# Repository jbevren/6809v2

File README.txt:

6809v2 single-board computer

(c) 2018 David Wood

This system is a 3.68mhz 6809-based microcomputer with 128k RAM and 8K rom.  It is intended to run 6809-based operating systems that run within 64k of RAM such as FLEX or OS-9 Level I.

All I/O services are provided via a 68681 DUART, either via one of its serial ports or via the extra GPIO pins on the device.

This documentation is primarily a placeholder and will likely be improved as time goes on(TM). ;-)

System memory map:

0000-DFFF	System RAM
E000-FEFF	System ROM  (ROMON=high) or System RAM(ROMON=low)
FF00-FF0F	68681 DUART (see below for I/O definitions)
FF10-FFDF	reserved: Don't use
FFE0-FFFF	System ROM  (ROMON=high) or System RAM(ROMON=low)

DUART I/O Map:
IP0		CTS port A
IP1		CTS port B
IP2		DCD port A (not routed)
IP3		DCD port B (not routed)
IP4		n/c
IP5		SD Data input	Input from Micro SD

OP0		RTS port A
OP1		RTS port B
OP2		RAM A16		A16 to RAM
OP3		RAM A17		A17 to RAM (128k has CE2 here)
OP4		ROMON		High enables the 2764 eprom
OP5		SDCK		Clock output to Micro SD
OP6		SDDO		Data output to Micro SD
OP7		SDCS		Chip select output to Micro SD
		NOTE: The 68681 sets all outputs high on reset
		NOTE: The 68681 inverts its output port bits

A summary of programming-related information is also printed on the pcb.

The memory fitted with a standard 128k-256k sram.  A 512k device can be fitted but the board lacks sufficient hardware to bankswitch more than 256k.
A jumper bridge under the SRAM will allow disconnecting A18 from ground.

Directories:
kicad/		Kicad v<5.0 files used to design the board
sbug/		S-BUG port to the 6809v2 SBC (working)
tests/		Prototype test code segments
sdcard/		SD-Card code (not yet finished)

** Many thanks to Dolo@hackaday.IO for the sdcard sample code and permission for the author to use it as long as the code for the firmware remains free and open! **

License: CC:SA license v4.0
I encourage the sharing and adaptation of this design as long as some credit to me is given in the firmware and/or board design.

Reach me at jbevren@gmail.com

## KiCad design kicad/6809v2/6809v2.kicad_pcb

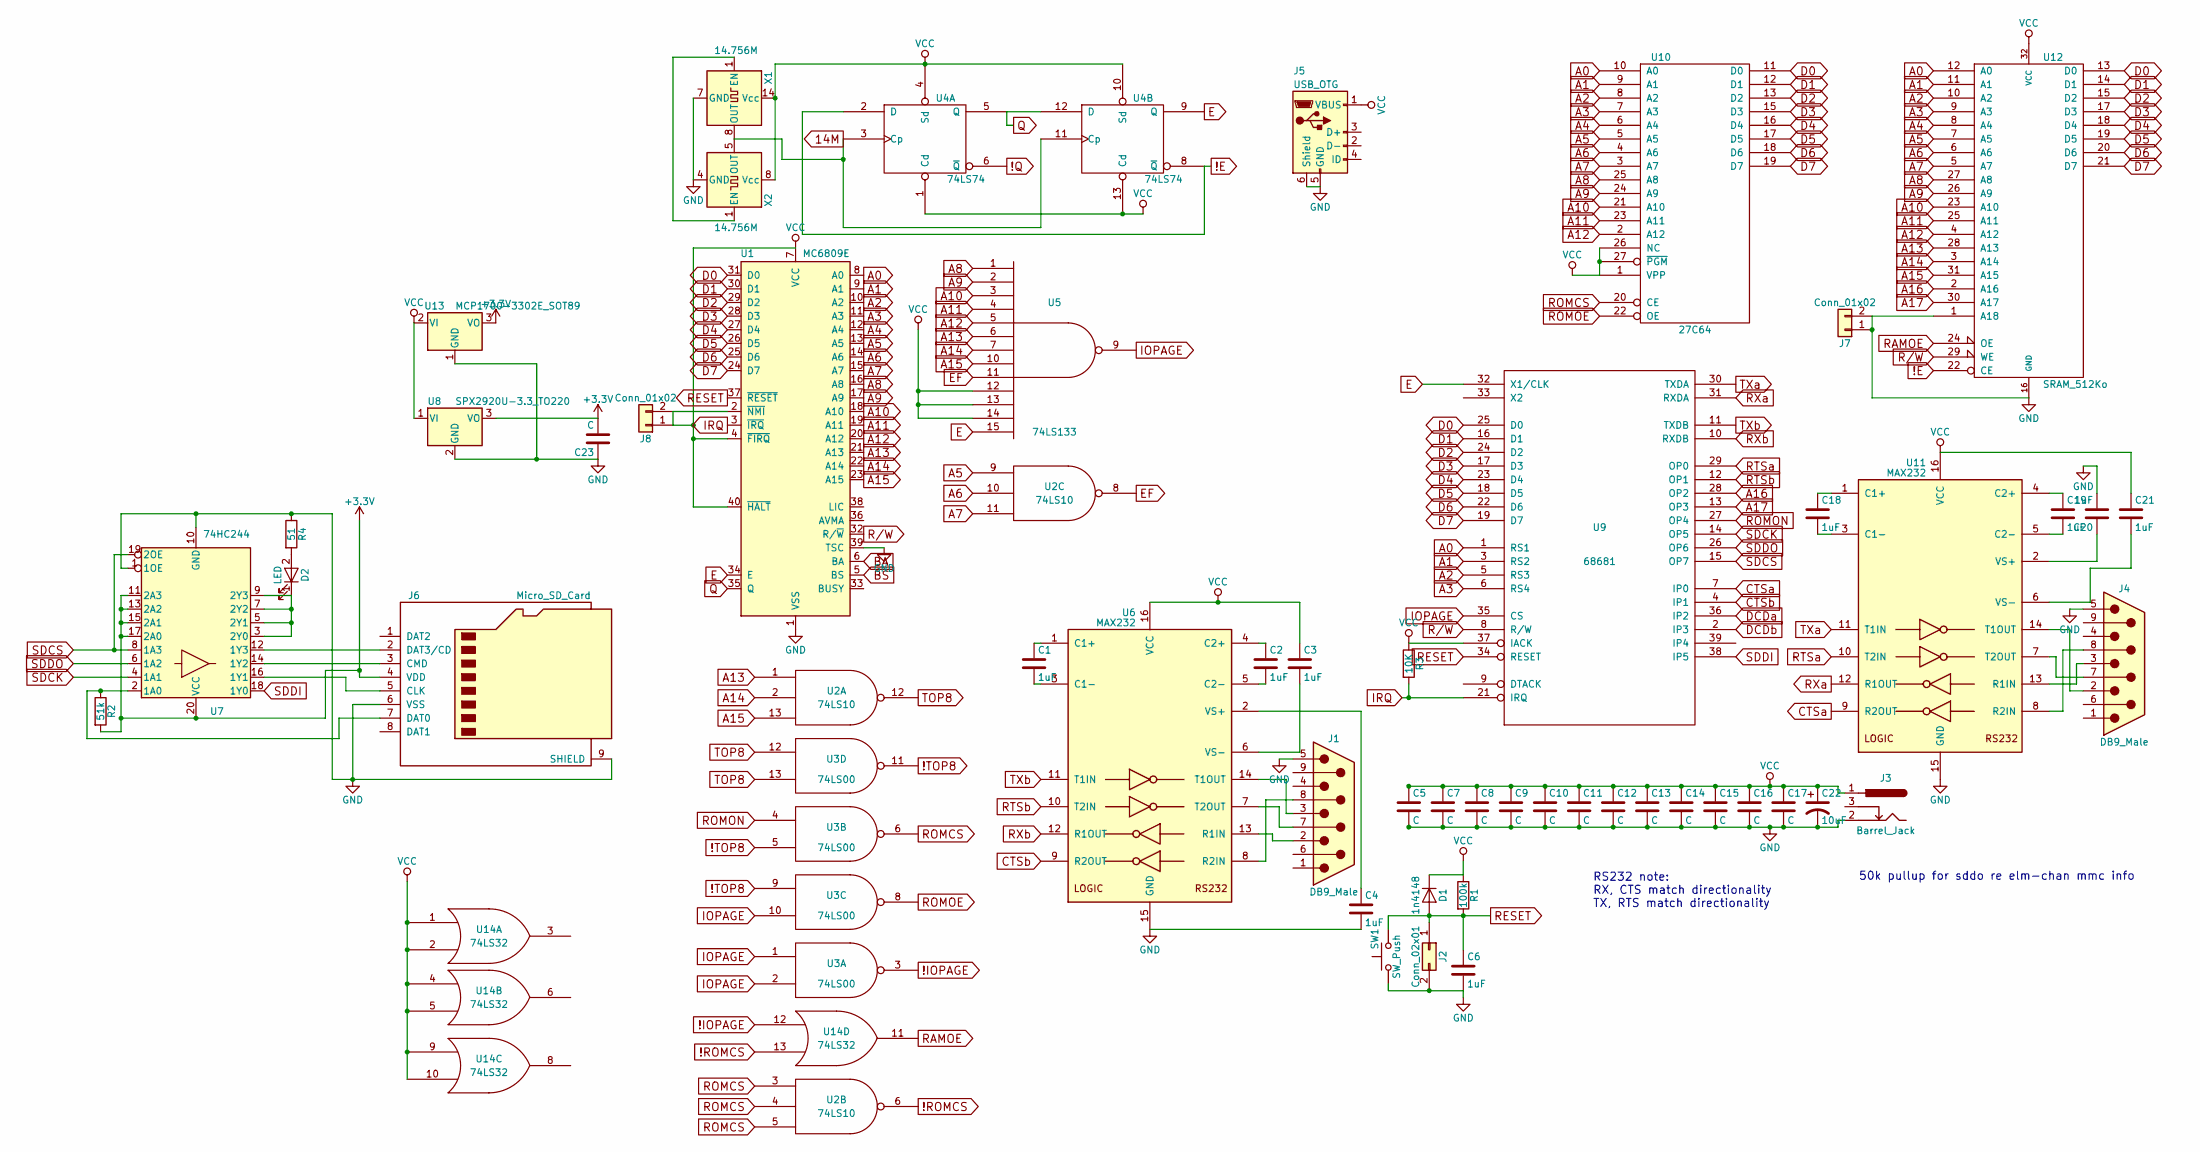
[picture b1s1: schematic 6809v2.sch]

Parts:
C1, C2, C3, C4, C18, C19, C20, C21: 1uF; CP_Radial_D5.0mm_P2.00mm
C5, C7, C8, C9, C10, C11, C12, C13, C14, C15, C16, C17: C; C_Disc_D5.0mm_W2.5mm_P2.50mm
C6: 1uF; C_Disc_D5.0mm_W2.5mm_P2.50mm
C22: 10uF; CP_Radial_D5.0mm_P2.50mm
C23: C; C_Disc_D5.0mm_W2.5mm_P5.00mm
D1: 1n4148; D_A-405_P7.62mm_Horizontal
D2: LED; LED_D5.0mm
J1, J4: DB9_Male; DB9M_CI
J2: Conn_02x01; Pin_Header_Straight_2x01_Pitch2.54mm
J3: Barrel_Jack; BARREL_JACK
J5: USB_OTG; USB_Micro-B_Molex_47346-0001
J6: Micro_SD_Card; MicroSd_Wurth_693072010801
J7, J8: Conn_01x02; Test_Point_2Pads_Pitch2.54mm_Drill0.8mm
R1: 100k; R_Axial_DIN0207_L6.3mm_D2.5mm_P2.54mm_Vertical
R2: 51k; R_1206_HandSoldering
R3: 10K; R_Axial_DIN0207_L6.3mm_D2.5mm_P7.62mm_Horizontal
R4: 51; R_1206_HandSoldering
SW1: SW_Push; SW_PUSH_6mm
U1: MC6809E; DIP-40_W15.24mm
U2: 74LS10; DIP-14_W7.62mm
U3: 74LS00; DIP-14_W7.62mm
U4: 74LS74; DIP-14_W7.62mm
U5: 74LS133; DIP-16_W7.62mm
U6, U11: MAX232; DIP-16_W7.62mm
U7: 74HC244; SSOP-20_4.4x6.5mm_Pitch0.65mm
U8: SPX2920U-3.3_TO220; TO-220-3_Vertical
U9: 68681; DIP-40_W15.24mm
U10: 27C64; DIP-28_W15.24mm
U12: SRAM_512Ko; DIP-32_W15.24mm
U13: MCP1700-3302E_SOT89; SOT-89-3
U14: 74LS32; DIP-14_W7.62mm
X1: 14.756M; Oscillator_DIP-14
X2: 14.756M; Oscillator_DIP-8

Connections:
14M: U4.3 (Cp), U4.11 (Cp), X1.8 (OUT), X2.5 (OUT)
!E: U4.2 (D), U4.8 (~Q), U12.22 (CE)
!IOPAGE: U3.3, U14.12
!Q: U4.6 (~Q)
!ROMCS: U2.6, U14.13
!TOP8: U3.5, U3.9, U3.11
+3V3: C23.2, J6.4 (VDD), R2.2, U7.11 (2A3), U7.13 (2A2), U7.15 (2A1), U7.17 (2A0), U7.20 (VCC), U8.3 (VO), U13.3 (VO)
A0: U1.8 (A0), U9.1 (RS1), U10.10 (A0), U12.12 (A0)
A1: U1.9 (A1), U9.3 (RS2), U10.9 (A1), U12.11 (A1)
A2: U1.10 (A2), U9.5 (RS3), U10.8 (A2), U12.10 (A2)
A3: U1.11 (A3), U9.6 (RS4), U10.7 (A3), U12.9 (A3)
A4: U1.12 (A4), U10.6 (A4), U12.8 (A4)
A5: U1.13 (A5), U2.9, U10.5 (A5), U12.7 (A5)
A6: U1.14 (A6), U2.10, U10.4 (A6), U12.6 (A6)
A7: U1.15 (A7), U2.11, U10.3 (A7), U12.5 (A7)
A8: U1.16 (A8), U5.1, U10.25 (A8), U12.27 (A8)
A9: U1.17 (A9), U5.2, U10.24 (A9), U12.26 (A9)
A10: U1.18 (A10), U5.3, U10.21 (A10), U12.23 (A10)
A11: U1.19 (A11), U5.4, U10.23 (A11), U12.25 (A11)
A12: U1.20 (A12), U5.5, U10.2 (A12), U12.4 (A12)
A13: U1.21 (A13), U2.1, U5.6, U12.28 (A13)
A14: U1.22 (A14), U2.2, U5.7, U12.3 (A14)
A15: U1.23 (A15), U2.13, U5.10, U12.31 (A15)
A16: U9.28 (OP2), U12.2 (A16)
A17: U9.13 (OP3), U12.30 (A17)
BA: U1.6 (BA)
BS: U1.5 (BS)
CTSa: U9.7 (IP0), U11.9 (R2OUT)
CTSb: U6.9 (R2OUT), U9.4 (IP1)
D0: U1.31 (D0), U9.25 (D0), U10.11 (D0), U12.13 (D0)
D1: U1.30 (D1), U9.16 (D1), U10.12 (D1), U12.14 (D1)
D2: U1.29 (D2), U9.24 (D2), U10.13 (D2), U12.15 (D2)
D3: U1.28 (D3), U9.17 (D3), U10.15 (D3), U12.17 (D3)
D4: U1.27 (D4), U9.23 (D4), U10.16 (D4), U12.18 (D4)
D5: U1.26 (D5), U9.18 (D5), U10.17 (D5), U12.19 (D5)
D6: U1.25 (D6), U9.22 (D6), U10.18 (D6), U12.20 (D6)
D7: U1.24 (D7), U9.19 (D7), U10.19 (D7), U12.21 (D7)
DCDa: U9.36 (IP2)
DCDb: U9.2 (IP3)
E: U1.34 (E), U4.9 (Q), U5.15, U9.32 (X1/CLK)
EF: U2.8, U5.11
GND: C4.2, C5.2, C6.2, C7.2, C8.2, C9.2, C10.2, C11.2, C12.2, C13.2, C14.2, C15.2, C16.2, C17.2, C20.2, C22.2, C23.1, J1.5, J2.2, J3.2, J4.5, J5.5 (GND), J5.6 (Shield), J6.6 (VSS), J6.9 (SHIELD), J7.1, J7.2, R4.1, SW1.1, U1.1 (VSS), U1.39 (TSC), U2.7 (GND), U3.7 (GND), U4.7 (GND), U5.8 (GND), U6.15 (GND), U7.1 (1OE), U7.10 (GND), U8.2 (GND), U9.20 (GND), U10.14 (GND), U11.15 (GND), U12.1 (A18), U12.16 (GND), U13.1 (GND), U14.7 (GND), X1.7 (GND), X2.4 (GND)
IOPAGE: U3.1, U3.2, U3.10, U5.9, U9.35 (CS)
IRQ: R3.2, U1.3 (~IRQ), U9.21 (IRQ)
unnamed: C1.1, U6.1 (C1+)
unnamed: C1.2, U6.3 (C1-)
unnamed: C2.1, U6.4 (C2+)
unnamed: C2.2, U6.5 (C2-)
unnamed: C3.2, U6.6 (VS-)
unnamed: C4.1, U6.2 (VS+)
unnamed: C18.1, U11.1 (C1+)
unnamed: C18.2, U11.3 (C1-)
unnamed: C19.1, U11.4 (C2+)
unnamed: C19.2, U11.5 (C2-)
unnamed: C20.1, U11.2 (VS+)
unnamed: C21.2, U11.6 (VS-)
unnamed: D2.1 (K), U7.3 (2Y0), U7.5 (2Y1), U7.7 (2Y2), U7.9 (2Y3)
unnamed: D2.2 (A), R4.2
unnamed: J1.2, U6.13 (R1IN)
unnamed: J1.3, U6.14 (T1OUT)
unnamed: J1.7, U6.7 (T2OUT)
unnamed: J1.8, U6.8 (R2IN)
unnamed: J4.2, U11.14 (T1OUT)
unnamed: J4.3, U11.13 (R1IN)
unnamed: J4.7, U11.7 (T2OUT)
unnamed: J4.8, U11.8 (R2IN)
unnamed: J6.2 (DAT3/CD), U7.12 (1Y3)
unnamed: J6.3 (CMD), U7.14 (1Y2)
unnamed: J6.5 (CLK), U7.16 (1Y1)
unnamed: J6.7 (DAT0), R2.1, U7.2 (1A0)
unnamed: X1.1 (EN), X2.1 (EN)
Q: U1.35 (Q), U4.5 (Q), U4.12 (D)
R/W: U1.32 (R/~W), U9.8 (R/W), U12.29 (WE)
RAMOE: U12.24 (OE), U14.11
RESET: C6.1, D1.2 (A), J2.1, R1.2, SW1.2, U1.37 (~RESET), U9.34 (RESET)
ROMCS: U2.3, U2.4, U2.5, U3.6, U10.20 (CE)
ROMOE: U3.8, U10.22 (OE)
ROMON: U3.4, U9.27 (OP4)
RTSa: U9.29 (OP0), U11.10 (T2IN)
RTSb: U6.10 (T2IN), U9.12 (OP1)
RXa: U9.31 (RXDA), U11.12 (R1OUT)
RXb: U6.12 (R1OUT), U9.10 (RXDB)
SDCK: U7.4 (1A1), U9.14 (OP5)
SDCS: U7.8 (1A3), U7.19 (2OE), U9.15 (OP7)
SDDI: U7.18 (1Y0), U9.38 (IP5)
SDDO: U7.6 (1A2), U9.26 (OP6)
TOP8: U2.12, U3.12, U3.13
TXa: U9.30 (TXDA), U11.11 (T1IN)
TXb: U6.11 (T1IN), U9.11 (TXDB)
VCC: C3.1, C5.1, C7.1, C8.1, C9.1, C10.1, C11.1, C12.1, C13.1, C14.1, C15.1, C16.1, C17.1, C21.1, C22.1, D1.1 (K), J3.1, J5.1 (VBUS), J8.1, J8.2, R1.1, R3.1, U1.2 (~NMI), U1.4 (~FIRQ), U1.7 (VCC), U1.40 (~HALT), U2.14 (VCC), U3.14 (VCC), U4.1 (Cd), U4.4 (Sd), U4.10 (Sd), U4.13 (Cd), U4.14 (VCC), U5.12, U5.13, U5.14, U5.16 (VCC), U6.16 (VCC), U8.1 (VI), U9.37 (IACK), U9.40 (VCC), U10.1 (VPP), U10.26 (NC), U10.27 (~PGM), U10.28 (VCC), U11.16 (VCC), U12.32 (VCC), U13.2 (VI), U14.1, U14.2, U14.4, U14.5, U14.9, U14.10, U14.14 (VCC), X1.14 (Vcc), X2.8 (Vcc)

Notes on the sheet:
50k pullup for sddo re elm-chan mmc info
RS232 note: RX, CTS match directionality TX, RTS match directionality

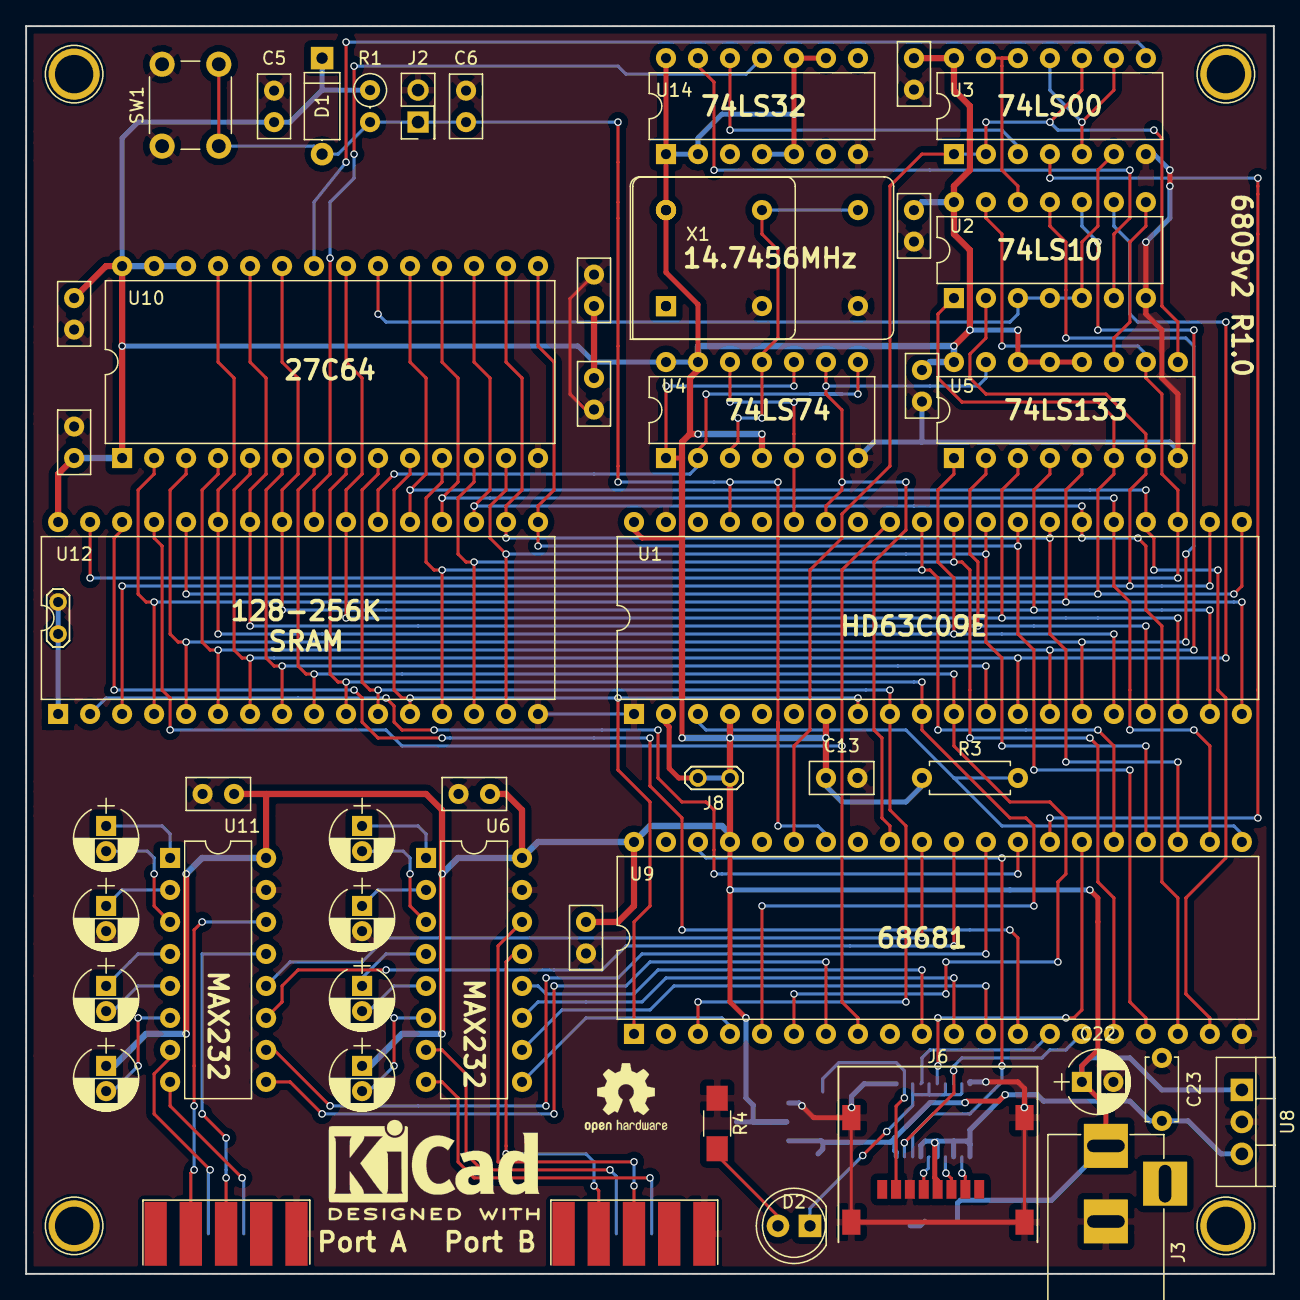
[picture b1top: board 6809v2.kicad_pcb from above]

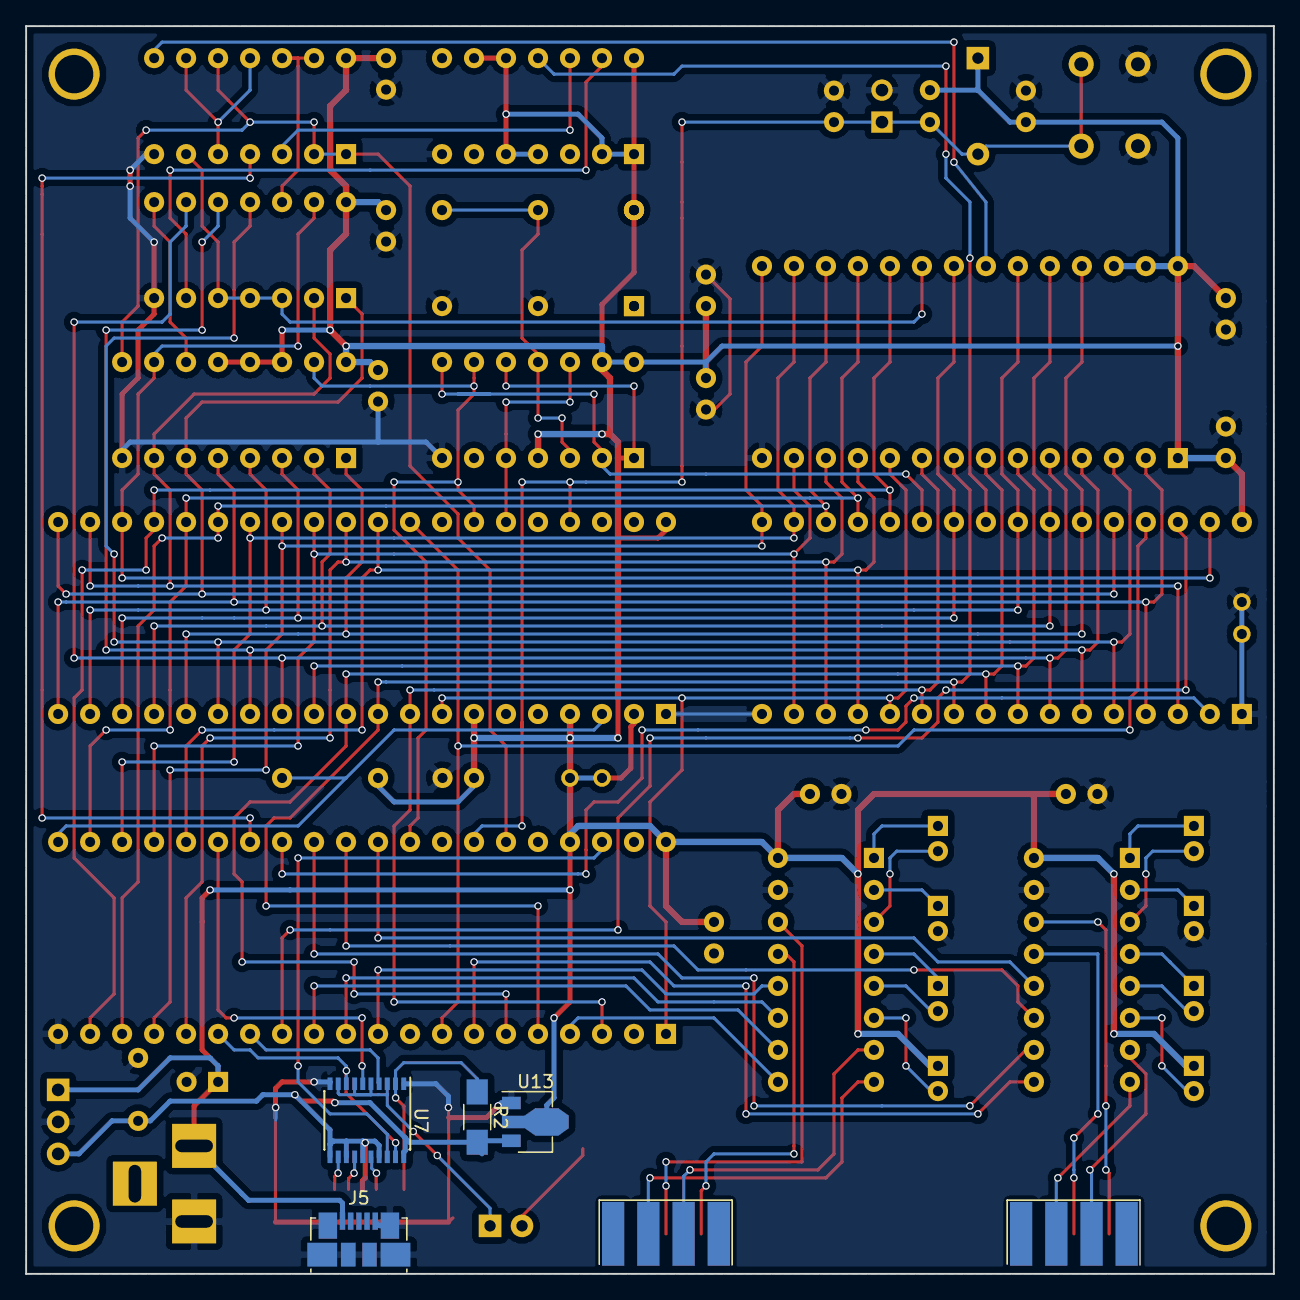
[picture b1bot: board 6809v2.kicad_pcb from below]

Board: 2 copper layers, 99.1 x 99.1 mm, 54 parts (4 on the bottom side), 85 nets.

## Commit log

2018-08-30 Didn't take long to end up with a typo.
2018-09-13 Release for VCFMW 13
2018-09-16 add email address, oops
2018-09-23 fix CPU name typo
2018-10-16 add PDF's to be friendly
